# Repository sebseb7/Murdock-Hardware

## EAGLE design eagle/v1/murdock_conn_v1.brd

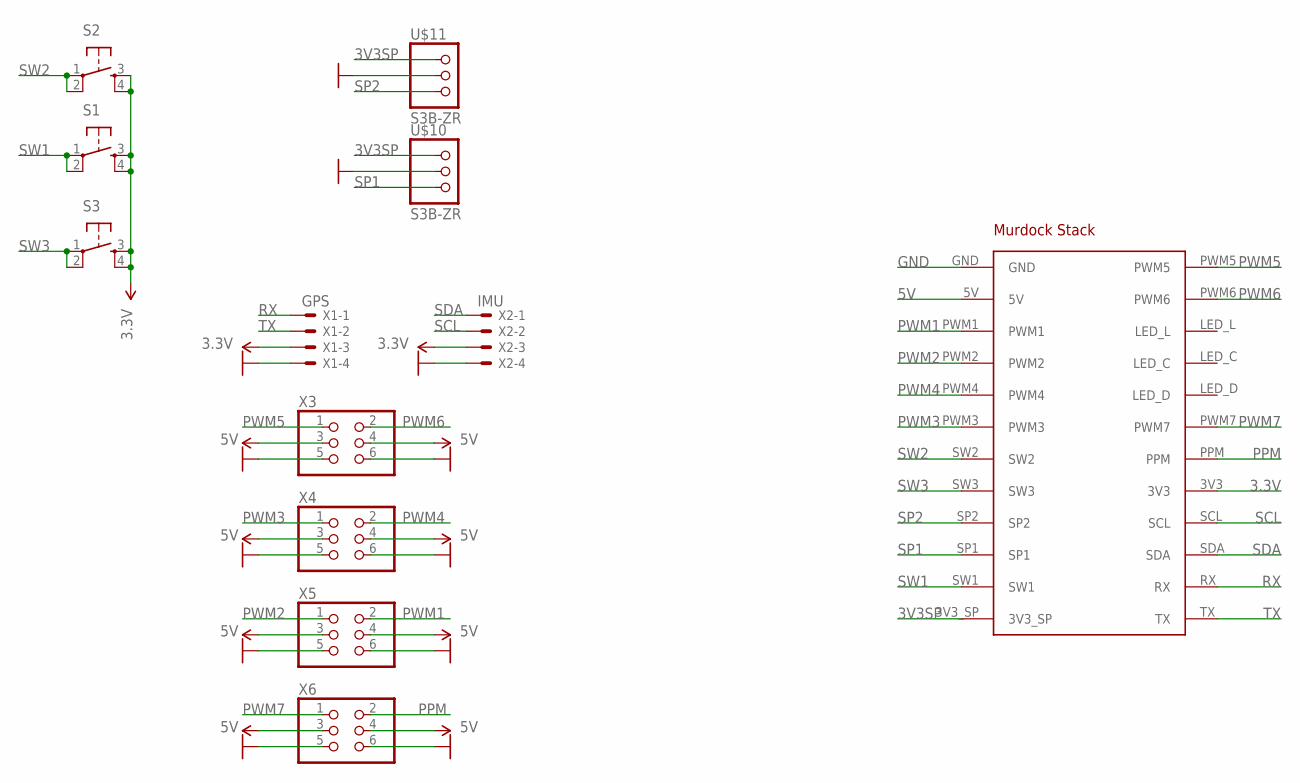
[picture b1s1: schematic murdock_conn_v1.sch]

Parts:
S1, S2, S3: LSH
U$10, U$11: S3B-ZR
X1: GPS; 70553-04
X2: IMU; 70553-04
X3, X4, X5, X6: PINHD-2X3/90; 2X03/90
X7: MURDOCK_STACK

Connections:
3.3V: S1.3, S1.4, S2.3, S2.4, S3.3, S3.4, X1.3, X2.3, X7.3V3
3V3SP: U$10.1, U$11.1, X7.3V3_SP
5V: X3.3, X3.4, X4.3, X4.4, X5.3, X5.4, X6.3, X6.4, X7.5V
GND: U$10.2, U$11.2, X1.4, X2.4, X3.5, X3.6, X4.5, X4.6, X5.5, X5.6, X6.5, X6.6, X7.GND
PPM: X6.2, X7.PPM
PWM1: X5.2, X7.PWM1
PWM2: X5.1, X7.PWM2
PWM3: X4.1, X7.PWM3
PWM4: X4.2, X7.PWM4
PWM5: X3.1, X7.PWM5
PWM6: X3.2, X7.PWM6
PWM7: X6.1, X7.PWM7
RX: X1.1, X7.RX
SCL: X2.2, X7.SCL
SDA: X2.1, X7.SDA
SP1: U$10.3, X7.SP1
SP2: U$11.3, X7.SP2
SW1: S1.1, S1.2, X7.SW1
SW2: S2.1, S2.2, X7.SW2
SW3: S3.1, S3.2, X7.SW3
TX: X1.2, X7.TX

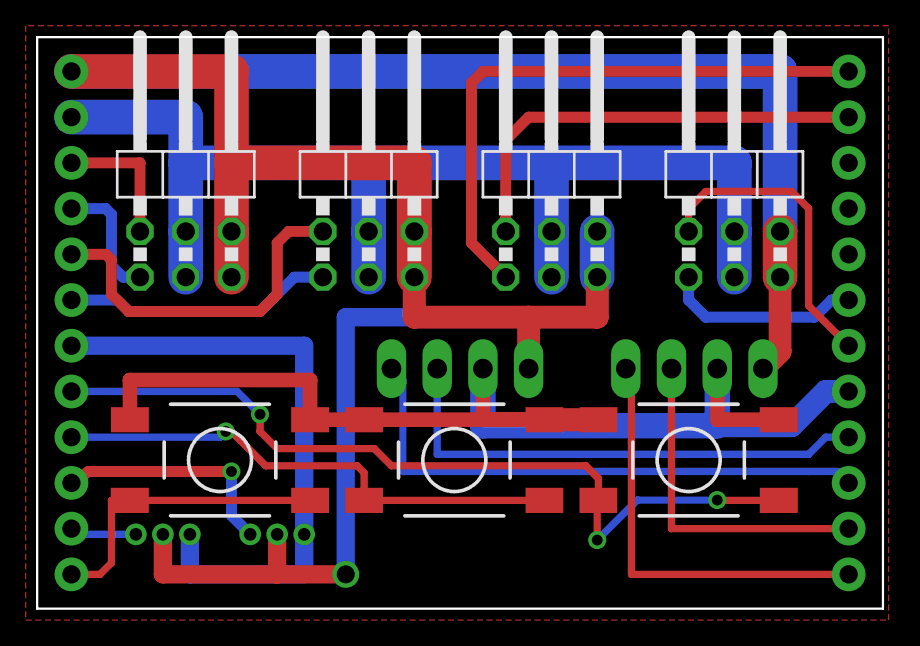
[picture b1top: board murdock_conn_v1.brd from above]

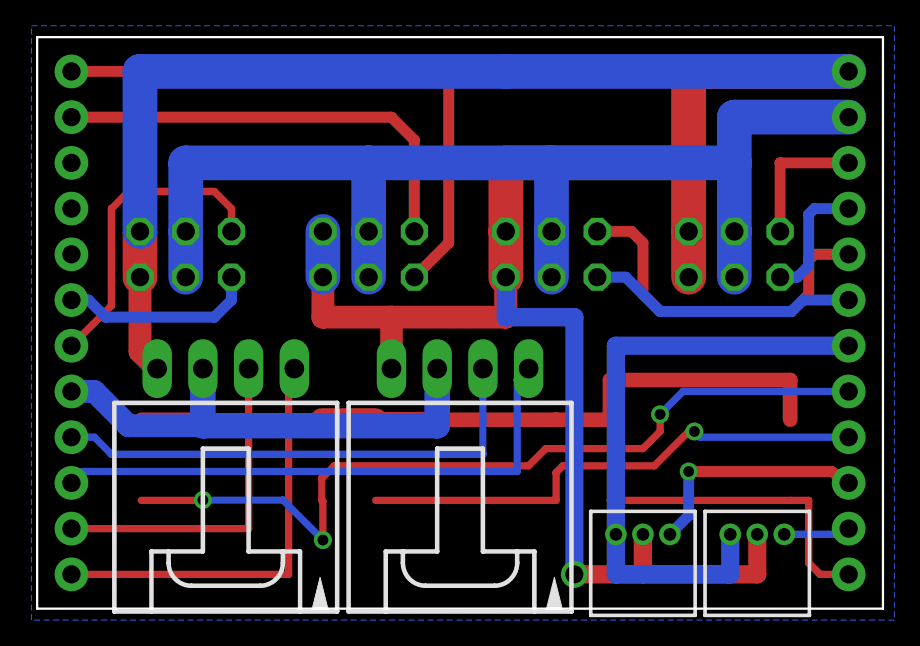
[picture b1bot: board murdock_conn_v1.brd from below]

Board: 2 copper layers, 47.0 x 31.8 mm, 12 parts (4 on the bottom side), 21 nets.

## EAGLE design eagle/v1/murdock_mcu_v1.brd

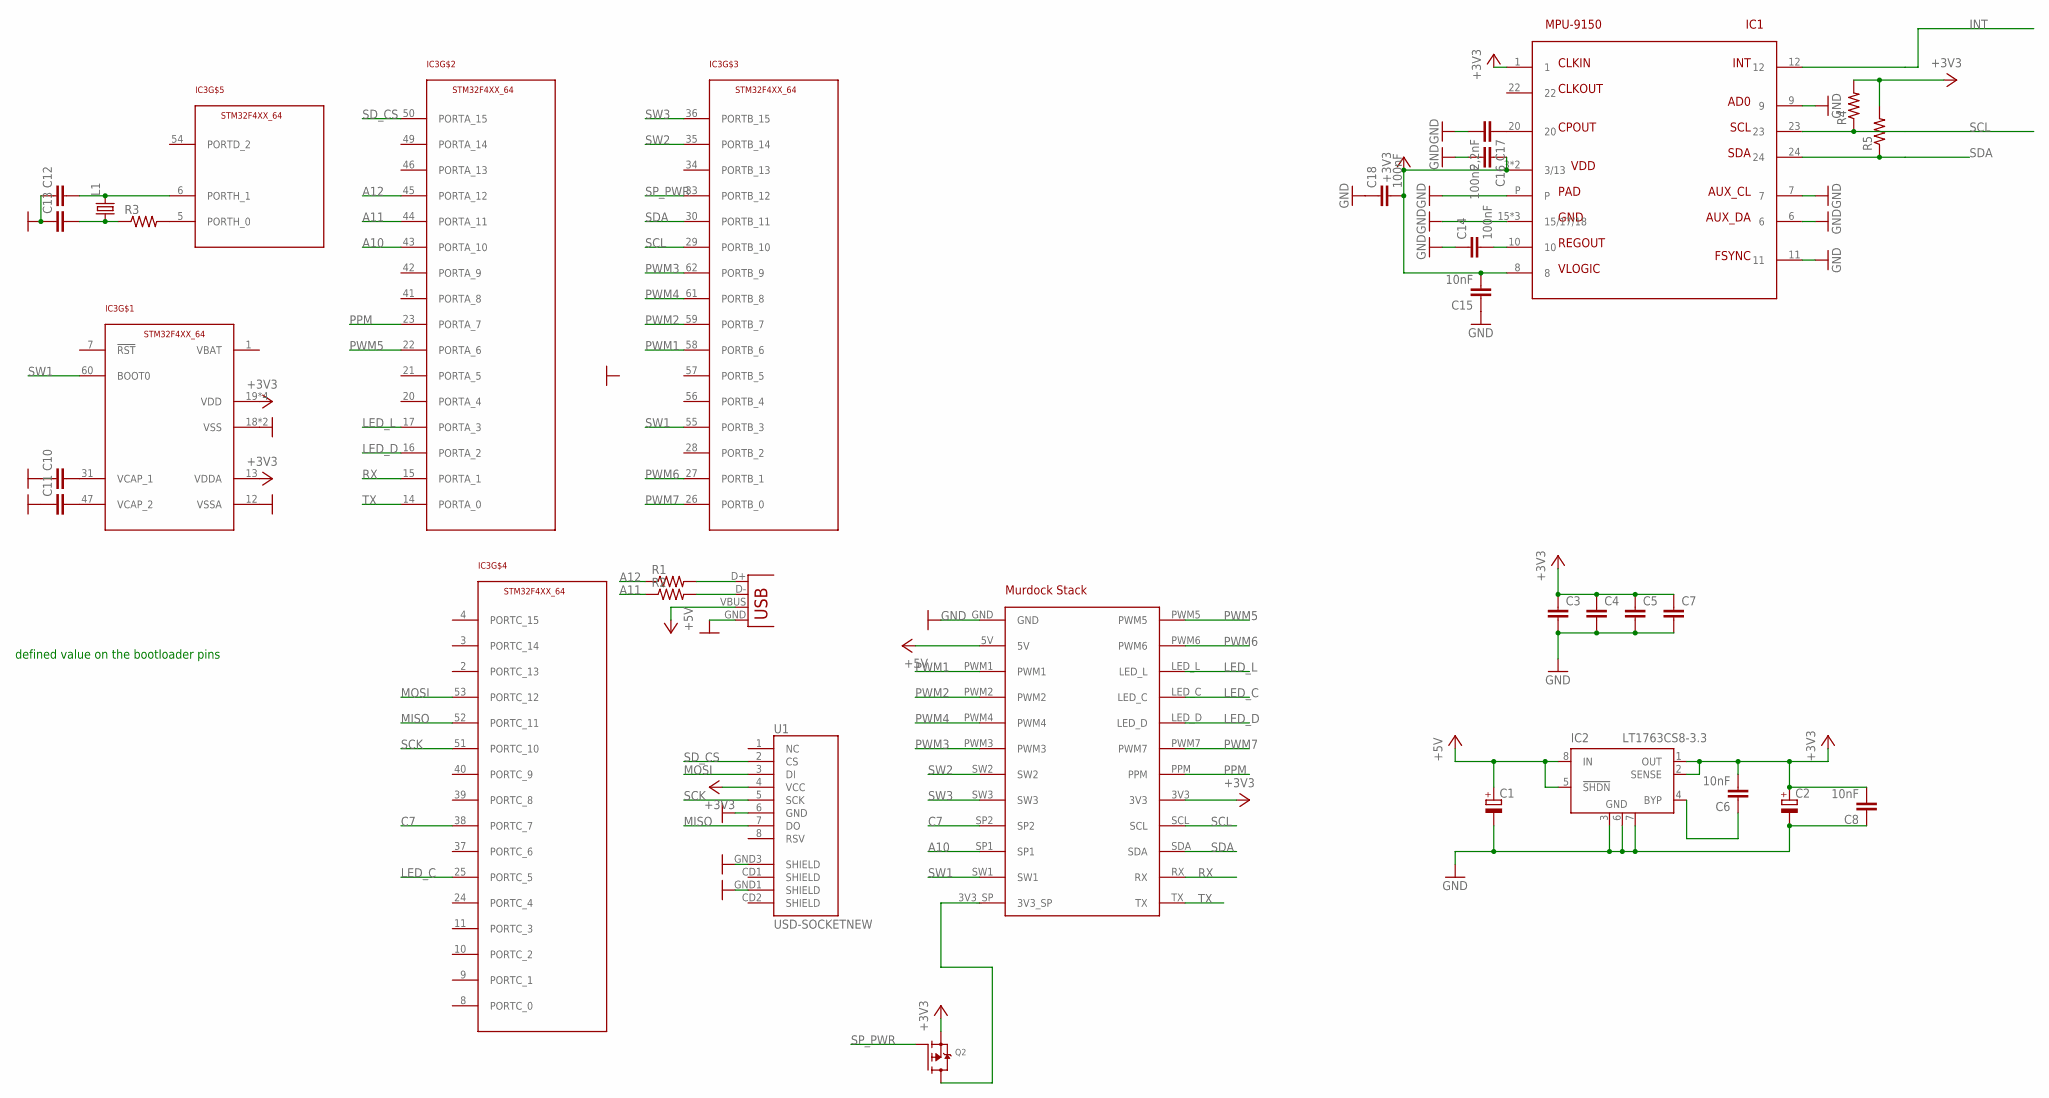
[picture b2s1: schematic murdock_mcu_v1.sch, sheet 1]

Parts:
C1, C2: CPOL-EUSMCD; SMC_D
C3, C4, C5, C7, C12, C13: CAP0402-CAP; 0402-CAP
C6, C8: 10nF; C0402
C10, C11: CAP0805; 0805
C14, C16, C18: 100nF; 0402-CAP
C15: 10nF; 0402-CAP
C17: 2,2nF; 0402-CAP
IC1: MPU-9150; QFN24
IC2: LT1763CS8-3.3; SOIC8
IC3: STM32F4XX_64; TQFP64
L1: X22-OSCILLATOR; X22
Q2: MOSFET-P; SOT23-R
R1, R2, R3, R4, R5: RESISTOR0402-RES; 0402-RES
U1: USD-SOCKETNEW; MICRO-SD-SOCKET-PP
X1: USBSMD; USB-MINIB
X2: MURDOCK_STACK

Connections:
+3V3: C2.+, C3.1, C4.1, C5.1, C6.2, C7.1, C8.2, C15.2, C16.1, C18.2, IC1.1, IC1.3 (3/13), IC1.8, IC1.13 (3/13), IC2.1 (OUT), IC2.2 (SENSE), IC3.13 (VDDA), IC3.19 (VDD), IC3.32 (VDD), IC3.48 (VDD), IC3.64 (VDD), Q2.2 (S), R4.2, R5.2, U1.4 (VCC), X2.3V3
+5V: C1.+, IC2.5 (!SHDN), IC2.8 (IN), X1.VBUS, X2.5V
A10: IC3.43 (PORTA_10), X2.SP1
A11: IC3.44 (PORTA_11), R2.1
A12: IC3.45 (PORTA_12), R1.1
C7: IC3.38 (PORTC_7), X2.SP2
GND: C1.-, C2.-, C3.2, C4.2, C5.2, C7.2, C8.1, C10.1, C11.1, C12.1, C13.1, C14.1, C15.1, C16.2, C17.2, C18.1, IC1.6, IC1.7, IC1.9, IC1.11, IC1.15 (15/17/18), IC1.17 (15/17/18), IC1.18 (15/17/18), IC1.P, IC2.3 (GND), IC2.6 (GND), IC2.7 (GND), IC3.12 (VSSA), IC3.18 (VSS), IC3.63 (VSS), U1.6 (GND), U1.GND1 (SHIELD), U1.GND3 (SHIELD), X1.GND, X2.GND
INT: IC1.12
LED_C: IC3.25 (PORTC_5), X2.LED_C
LED_D: IC3.16 (PORTA_2), X2.LED_D
LED_L: IC3.17 (PORTA_3), X2.LED_L
MISO: IC3.52 (PORTC_11), U1.7 (DO)
MOSI: IC3.53 (PORTC_12), U1.3 (DI)
unnamed: R2.2, X1.D-
unnamed: R1.2, X1.D+
unnamed: C10.2, IC3.31 (VCAP_1)
unnamed: C11.2, IC3.47 (VCAP_2)
unnamed: IC3.5 (PORTH_0), R3.2
unnamed: C13.2, L1.1, R3.1
unnamed: C12.2, IC3.6 (PORTH_1), L1.3 (2)
unnamed: Q2.3 (D), X2.3V3_SP
unnamed: C14.2, IC1.10
unnamed: C17.1, IC1.20
unnamed: C6.1, IC2.4 (BYP)
PPM: IC3.23 (PORTA_7), X2.PPM
PWM1: IC3.58 (PORTB_6), X2.PWM1
PWM2: IC3.59 (PORTB_7), X2.PWM2
PWM3: IC3.62 (PORTB_9), X2.PWM3
PWM4: IC3.61 (PORTB_8), X2.PWM4
PWM5: IC3.22 (PORTA_6), X2.PWM5
PWM6: IC3.27 (PORTB_1), X2.PWM6
PWM7: IC3.26 (PORTB_0), X2.PWM7
RX: IC3.15 (PORTA_1), X2.RX
SCK: IC3.51 (PORTC_10), U1.5 (SCK)
SCL: IC1.23, IC3.29 (PORTB_10), R4.1, X2.SCL
SDA: IC1.24, IC3.30 (PORTB_11), R5.1, X2.SDA
SD_CS: IC3.50 (PORTA_15), U1.2 (CS)
SP_PWR: IC3.33 (PORTB_12), Q2.1 (G)
SW1: IC3.55 (PORTB_3), IC3.60 (BOOT0), X2.SW1
SW2: IC3.35 (PORTB_14), X2.SW2
SW3: IC3.36 (PORTB_15), X2.SW3
TX: IC3.14 (PORTA_0), X2.TX

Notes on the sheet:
defined value on the bootloader pins

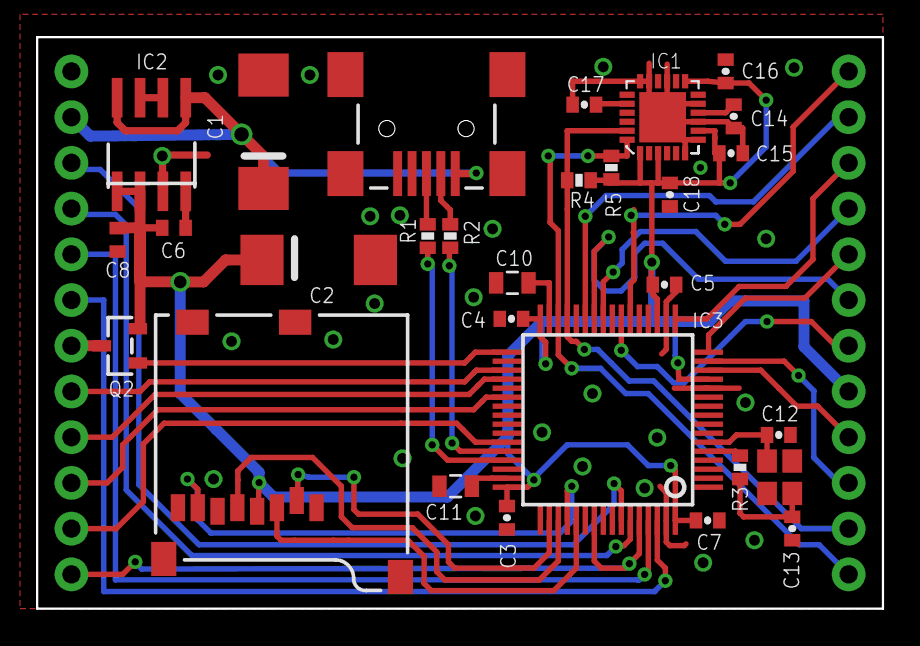
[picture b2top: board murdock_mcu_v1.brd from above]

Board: 2 copper layers, 47.0 x 31.8 mm, 31 parts (1 on the bottom side), 41 nets.

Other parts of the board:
U$1: C3D2_LOGO_SMALL

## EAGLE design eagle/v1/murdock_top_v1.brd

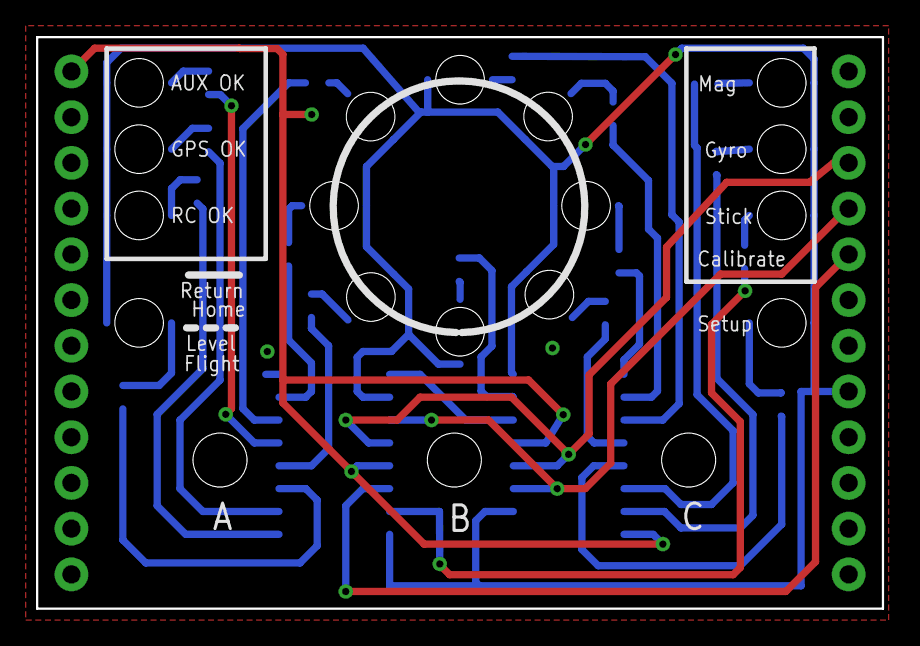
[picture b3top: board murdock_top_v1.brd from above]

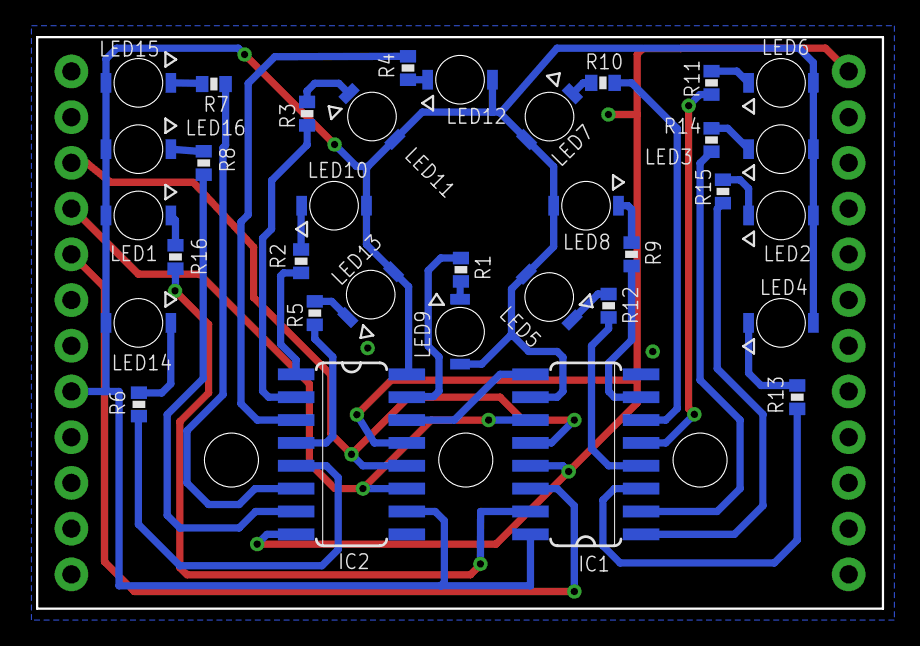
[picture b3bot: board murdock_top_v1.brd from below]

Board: 2 copper layers, 47.0 x 31.8 mm, 35 parts (34 on the bottom side), 38 nets.

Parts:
IC1, IC2: 74HC595D; SO16
LED1, LED2, LED3, LED4, LED5, LED6, LED7, LED8, LED9, LED10, LED11, LED12, LED13, LED14, LED15, LED16: LGM47K
R1, R2, R3, R4, R5, R6, R7, R8, R9, R10, R11, R12, R13, R14, R15, R16: 0402-RES
X1: MURDOCK_STACK

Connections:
3.3V: IC1.10, IC1.16, IC2.10, IC2.16, LED1.A, LED2.A, LED3.A, LED4.A, LED5.A, LED6.A, LED7.A, LED8.A, LED9.A, LED10.A, LED11.A, LED12.A, LED13.A, LED14.A, LED15.A, LED16.A, X1.3V3
GND: IC1.8, IC1.13, IC2.8, IC2.13, X1.GND
LED_C: IC1.11, IC2.11, X1.LED_C
LED_D: IC1.14, X1.LED_D
LED_L: IC1.12, IC2.12, X1.LED_L
unnamed: IC1.9, IC2.14
unnamed: LED9.K, R1.2
unnamed: LED10.K, R2.2
unnamed: LED11.K, R3.2
unnamed: LED12.K, R4.2
unnamed: LED13.K, R5.2
unnamed: LED14.K, R6.2
unnamed: LED15.K, R7.2
unnamed: LED16.K, R8.2
unnamed: LED1.K, R16.2
unnamed: LED2.K, R15.2
unnamed: LED3.K, R14.2
unnamed: LED4.K, R13.2
unnamed: LED5.K, R12.2
unnamed: LED6.K, R11.2
unnamed: LED7.K, R10.2
unnamed: LED8.K, R9.2
Q0: IC2.15, R1.1
Q1: IC2.1, R2.1
Q2: IC2.2, R3.1
Q3: IC2.3, R4.1
Q4: IC2.4, R5.1
Q5: IC2.5, R6.1
Q6: IC2.6, R7.1
Q7: IC2.7, R8.1
QA: IC1.15, R16.1
QB: IC1.1, R15.1
QC: IC1.2, R14.1
QD: IC1.3, R13.1
QE: IC1.4, R12.1
QF: IC1.5, R11.1
QG: IC1.6, R10.1
QH: IC1.7, R9.1

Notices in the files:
parts and their libraries:
SparkFun-Aesthetics: Licensing: CC v3.0 Share-Alike You are welcome to use this library for commercial purposes.
microbuilder: This work is placed in the public domain, and may be freely used for commercial and non-commercial work with the following conditions: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
